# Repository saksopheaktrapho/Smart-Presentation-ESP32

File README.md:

# Smart-Presentation-ESP32

**Smart Presentation** is a Bluetooth keyboard that has three configurable buttons with one vibration motor. As the name suggests, this project goal is to make a presentation more easy.

**Smart Presentation** uses ESP32-PICO-D4 as its microcontroller with three buttons, a battery control charger, USB Type-C, MPU6050, and a vibration motor.

## 3D Model

## Feature
- Use **ESP32-PICO-D4** as the core controller.
- Have 3 configurable buttons that can work as any key on the keyboard. The button also have LED for indicator.
- Chip **MPU6050** on board help to detect the motion of device.
- Use **MCP73831** for battery charger.
- **USB Type-C** for programing and charge the battery.
- **Vibration Motor** for alert or some indicator.
- Connector for one cell Lithium Ion Battery.

## Video
Link to the assembly video of this project.
https://youtube.com/shorts/3c2iB_zuU0U?feature=share

## Images
Images of 3D Model

Pre-Assembly Image

Images of the Module

# Noticed
The PCB of this project is design using KiCad V6.
This project is under development and some of the function maybe not working properly. 😉

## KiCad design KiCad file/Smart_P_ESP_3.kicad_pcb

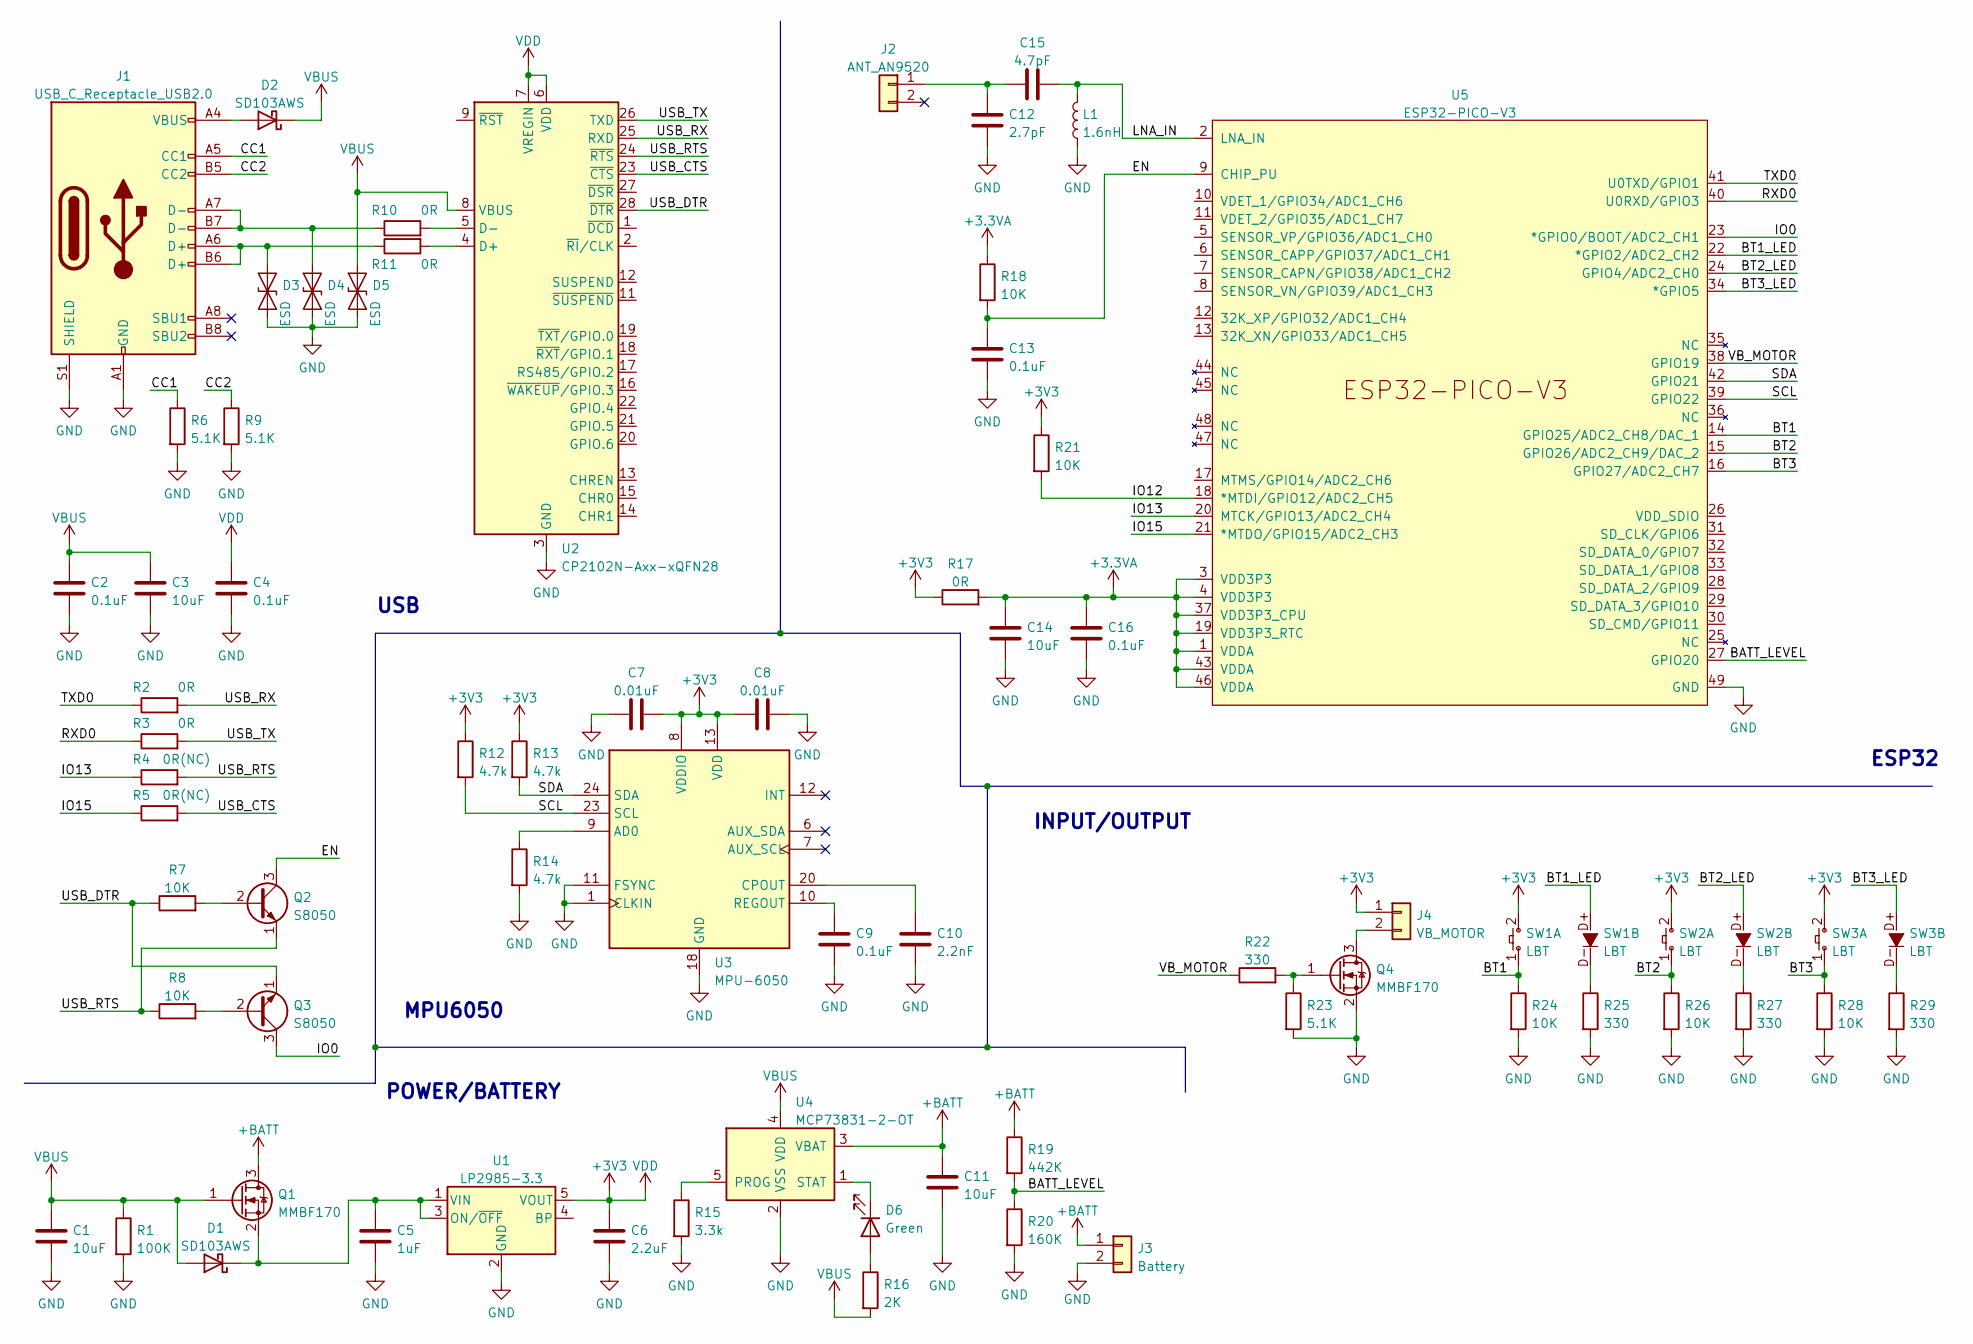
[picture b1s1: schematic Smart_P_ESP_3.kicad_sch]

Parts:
C1, C3, C11, C14: 10uF; C_1206_3216Metric
C2, C4, C9, C13, C16: 0.1uF; C_0603_1608Metric
C5: 1uF; C_1206_3216Metric
C6: 2.2uF; C_1206_3216Metric
C7, C8: 0.01uF; C_0603_1608Metric
C10: 2.2nF; C_0603_1608Metric
C12: 2.7pF; C_0603_1608Metric
C15: 4.7pF; C_0603_1608Metric
D1, D2: SD103AWS; D_SOD-323
D3, D4, D5: ESD; D_0603_1608Metric
D6: Green; LED_0603_1608Metric
J1: USB_C_Receptacle_USB2.0; USB_C_Receptacle_XKB_U262-16XN-4BVC11
J2: ANT_AN9520; AN9520_Rainsun
J3: Battery; Molex_CLIK-Mate_502386-0270_1x02-1MP_P1.25mm_Horizontal
J4: VB_MOTOR; Molex_CLIK-Mate_502386-0270_1x02-1MP_P1.25mm_Horizontal
L1: 1.6nH; L_0603_1608Metric
Q1, Q4: MMBF170; SOT-23
Q2, Q3: S8050; SOT-23
R1: 100K; R_0603_1608Metric
R2, R3, R10, R11, R17: 0R; R_0603_1608Metric
R4, R5: 0R(NC); R_0603_1608Metric
R6, R9, R23: 5.1K; R_0603_1608Metric
R7, R8, R18, R21, R24, R26, R28: 10K; R_0603_1608Metric
R12, R13, R14: 4.7k; R_0603_1608Metric
R15: 3.3k; R_0603_1608Metric
R16: 2K; R_0603_1608Metric
R19: 442K; R_0603_1608Metric
R20: 160K; R_0603_1608Metric
R22, R25, R27, R29: 330; R_0603_1608Metric
SW1, SW2, SW3: LBT; LED_Push_Button
U1: LP2985-3.3; SOT-23-5
U2: CP2102N-Axx-xQFN28; QFN-28-1EP_5x5mm_P0.5mm_EP3.35x3.35mm
U3: MPU-6050; InvenSense_QFN-24_4x4mm_P0.5mm
U4: MCP73831-2-OT; SOT-23-5
U5: ESP32-PICO-V3; QFN-48-1EP_7x7mm_P0.5mm_EP5.15x5.15mm

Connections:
+3.3VA: C14.1, C16.1, R17.2, R18.1, U5.1 (VDDA), U5.3 (VDD3P3), U5.4 (VDD3P3), U5.19 (VDD3P3_RTC), U5.37 (VDD3P3_CPU), U5.43 (VDDA), U5.46 (VDDA)
+3V3: C4.1, C6.1, C7.2, C8.1, J4.1, R12.1, R13.1, R17.1, R21.1, SW1.2, SW2.2, SW3.2, U1.5 (VOUT), U2.6 (VDD), U2.7 (VREGIN), U3.8 (VDDIO), U3.13 (VDD)
+BATT: C11.1, J3.1, Q1.3 (D), R19.1, U4.3 (VBAT)
/BATT_LEVEL: R19.2, R20.1, U5.27 (GPIO20)
/BT1: R24.1, SW1.1, U5.14 (GPIO25/ADC2_CH8/DAC_1)
/BT1_LED: SW1.D+, U5.22 (*GPIO2/ADC2_CH2)
/BT2: R26.1, SW2.1, U5.15 (GPIO26/ADC2_CH9/DAC_2)
/BT2_LED: SW2.D+, U5.24 (GPIO4/ADC2_CH0)
/BT3: R28.1, SW3.1, U5.16 (GPIO27/ADC2_CH7)
/BT3_LED: SW3.D+, U5.34 (*GPIO5)
/CC1: J1.A5 (CC1), R6.1
/CC2: J1.B5 (CC2), R9.1
/EN: C13.1, Q2.3 (C), R18.2, U5.9 (CHIP_PU)
/IO0: Q3.3 (C), U5.23 (*GPIO0/BOOT/ADC2_CH1)
/IO12: R21.2, U5.18 (*MTDI/GPIO12/ADC2_CH5)
/IO13: R4.1, U5.20 (MTCK/GPIO13/ADC2_CH4)
/IO15: R5.1, U5.21 (*MTDO/GPIO15/ADC2_CH3)
/LNA_IN: C15.2, L1.2, U5.2 (LNA_IN)
/RXD0: R3.1, U5.40 (U0RXD/GPIO3)
/SCL: R12.2, U3.23 (SCL), U5.39 (GPIO22)
/SDA: R13.2, U3.24 (SDA), U5.42 (GPIO21)
/TXD0: R2.1, U5.41 (U0TXD/GPIO1)
/USB_CTS: R5.2, U2.23 (~CTS)
/USB_DTR: Q3.1 (E), R7.1, U2.28 (~DTR)
/USB_RTS: Q2.1 (E), R4.2, R8.1, U2.24 (~RTS)
/USB_RX: R2.2, U2.25 (RXD)
/USB_TX: R3.2, U2.26 (TXD)
/VB_MOTOR: R22.1, U5.38 (GPIO19)
GND: C1.2, C2.2, C3.2, C4.2, C5.2, C6.2, C7.1, C8.2, C9.2, C10.2, C11.2, C12.2, C13.2, C14.2, C16.2, D3.1 (A1), D4.1 (A1), D5.1 (A1), J1.A1 (GND), J1.A12 (GND), J1.B1 (GND), J1.B12 (GND), J1.S1 (SHIELD), J3.2, L1.1, Q4.2 (S), R1.2, R6.2, R9.2, R14.2, R15.2, R20.2, R23.2, R24.2, R25.2, R26.2, R27.2, R28.2, R29.2, U1.2 (GND), U2.3 (GND), U2.29 (GND), U3.1 (CLKIN), U3.11 (FSYNC), U3.18 (GND), U4.2 (VSS), U5.49 (GND)
unnamed: C5.1, D1.1 (K), Q1.2 (S), U1.1 (VIN), U1.3 (ON/~OFF)
unnamed: C9.1, U3.10 (REGOUT)
unnamed: C10.1, U3.20 (CPOUT)
unnamed: C12.1, C15.1, J2.1
unnamed: D2.2 (A), J1.A4 (VBUS), J1.A9 (VBUS), J1.B4 (VBUS), J1.B9 (VBUS)
unnamed: D3.2 (A2), J1.A6 (D+), J1.B6 (D+), R11.1
unnamed: D4.2 (A2), J1.A7 (D-), J1.B7 (D-), R10.1
unnamed: D6.1 (K), U4.1 (STAT)
unnamed: D6.2 (A), R16.1
unnamed: J4.2, Q4.3 (D)
unnamed: Q2.2 (B), R7.2
unnamed: Q3.2 (B), R8.2
unnamed: Q4.1 (G), R22.2, R23.1
unnamed: R10.2, U2.5 (D-)
unnamed: R11.2, U2.4 (D+)
unnamed: R14.1, U3.9 (AD0)
unnamed: R15.1, U4.5 (PROG)
unnamed: R25.1, SW1.D-
unnamed: R27.1, SW2.D-
unnamed: R29.1, SW3.D-
VBUS: C1.1, C2.1, C3.1, D1.2 (A), D2.1 (K), D5.2 (A2), Q1.1 (G), R1.1, R16.2, U2.8 (VBUS), U4.4 (VDD)

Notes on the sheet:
USB
POWER/BATTERY
INPUT/OUTPUT
ESP32
MPU6050

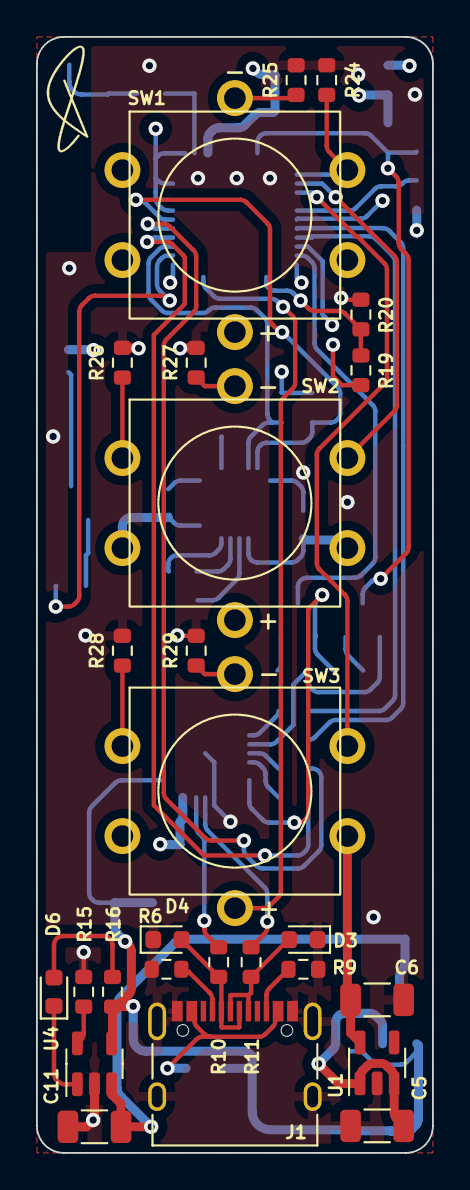
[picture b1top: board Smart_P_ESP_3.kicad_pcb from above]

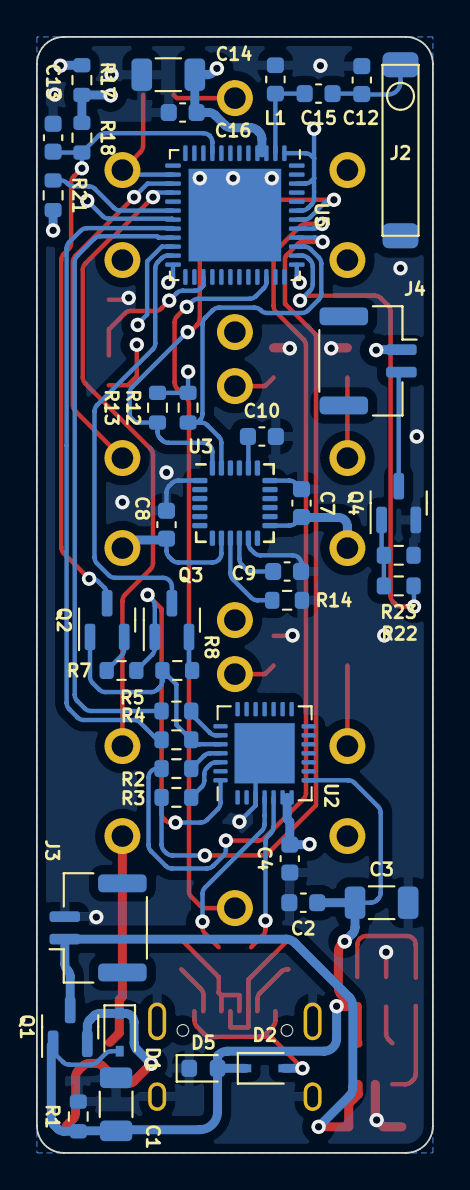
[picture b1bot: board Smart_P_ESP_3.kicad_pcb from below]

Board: 4 copper layers, 22.0 x 62.0 mm, 68 parts (42 on the bottom side), 50 nets.

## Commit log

2023-03-11 add kicad v6 files
2023-03-11 add 3d file
2023-03-12 Add images
2023-03-12 Add GERBER
2023-03-22 add some images
2023-03-24 REAL Module
